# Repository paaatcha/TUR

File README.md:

# University Robotic Tournament

In this repository, you can find the codes and files of the [UFES robotic team](http://www.erus.ufes.br/) developed to the III University Robotic Tournament (TUR, in Portuguese), at Federal University of Uberlândia, Brazil. This project was developed by a team composed by me, Guilherme Artém and Vanderlei Vieira.

The tournament's rules are described in [rules.pd](https://github.com/paaatcha/TUR/blob/master/rules.pdf). In brief, the competition was a robot race in which the track race had a line that the robot must follow. In addition, there were extra challenges such as slopes, dark parts, crossroads, dangers turns, etc. The robot needed to be **autonomous** and complete the track race as fast as possible.

The robot structure was developed using the 3D software [openScad](http://www.openscad.org/). Next, this structure was printed in a 3D printer and used as the robot "body".

The robot had 10 light sensors to track the line. We developed a PCB that you can find [here](http://github.com/paaatcha/TUR/eletronica). 

The robot had an Arduino Mega, in which we implemented a PID control using C++. You can check out code in this [folder](https://github.com/paaatcha/TUR/tree/master/programacao).

Later, this robot became my undergraduate thesis, in which is described more detailed [here](http://github.com/paaatcha/projeto-graduacao).

Robot version 1: (you may note that in this version the robot has an Arduino UNO and the light sensors PCB wasn't the one pictured above)

Robot final version: (now it has the Arduino Mega and the developed PCB)

Take look at the robot's performance on the official race track. It's very cool to see the PID working for the 90º turn.

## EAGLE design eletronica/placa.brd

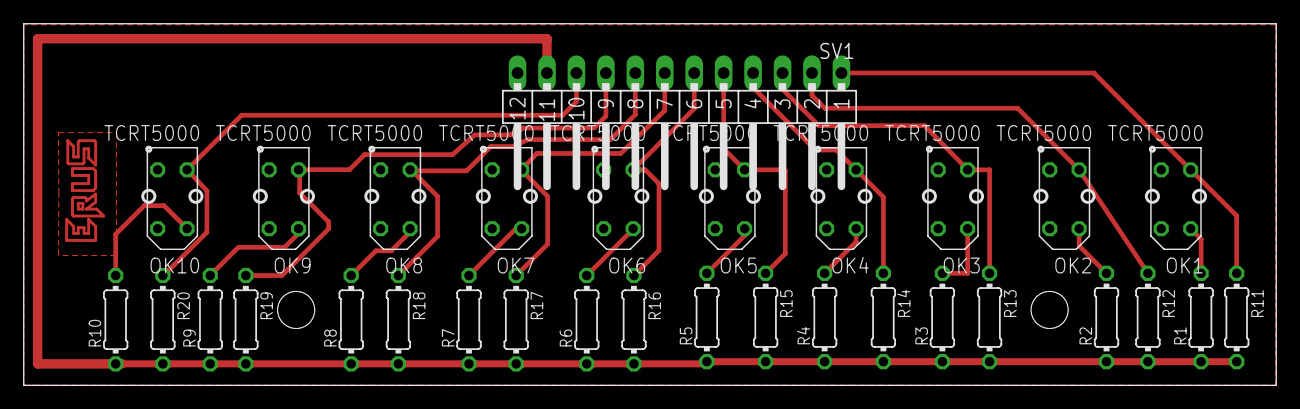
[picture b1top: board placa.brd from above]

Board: 2 copper layers, 108.0 x 31.2 mm, 31 parts (0 on the bottom side), 22 nets.

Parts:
OK1, OK2, OK3, OK4, OK5, OK6, OK7, OK8, OK9, OK10: TCRT5000
R1, R2, R3, R4, R5, R6, R7, R8, R9, R10, R11, R12, R13, R14, R15, R16, R17, R18, R19, R20: 0204/7
SV1: MA12-1W

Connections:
5V: R1.1, R2.1, R3.1, R4.1, R5.1, R6.1, R7.1, R8.1, R9.1, R10.1, R11.2, R12.2, R13.2, R14.2, R15.2, R16.2, R17.2, R18.2, R19.2, R20.2, SV1.11
GND: OK1.E, OK1.KATODA, OK2.E, OK2.KATODA, OK3.E, OK3.KATODA, OK4.E, OK4.KATODA, OK5.E, OK5.KATODA, OK6.E, OK6.KATODA, OK7.E, OK7.KATODA, OK8.E, OK8.KATODA, OK9.E, OK9.KATODA, OK10.E, OK10.KATODA, SV1.12
unnamed: OK2.A, R2.2
unnamed: OK1.C, R11.1, SV1.1
unnamed: OK1.A, R1.2
unnamed: OK3.A, R3.2
unnamed: OK4.A, R4.2
unnamed: OK5.A, R5.2
unnamed: OK6.A, R6.2
unnamed: OK7.A, R7.2
unnamed: OK8.A, R8.2
unnamed: OK9.A, R9.2
unnamed: OK10.A, R10.2
unnamed: OK2.C, R12.1, SV1.2
unnamed: OK3.C, R13.1, SV1.3
unnamed: OK8.C, R18.1, SV1.8
unnamed: OK10.C, R20.1, SV1.10
unnamed: OK4.C, R14.1, SV1.4
unnamed: OK5.C, R15.1, SV1.5
unnamed: OK6.C, R16.1, SV1.6
unnamed: OK7.C, R17.1, SV1.7
unnamed: OK9.C, R19.1, SV1.9

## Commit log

2018-07-17 figuras adicionadas
